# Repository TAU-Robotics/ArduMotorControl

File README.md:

# Discrete Control Lab
Discrete control experiment developed for the control lab at Tel Aviv University
The setup uses an Arduino Uno micro controller, micro dc gear motor with magnetic encoder and SparkFun Ardumoto shield.

The experiment has two parts, Simulation in simulink matlab and a hardware setup with arduino.

Simulation response:

Arduino response:

# HomeKit Motor Control

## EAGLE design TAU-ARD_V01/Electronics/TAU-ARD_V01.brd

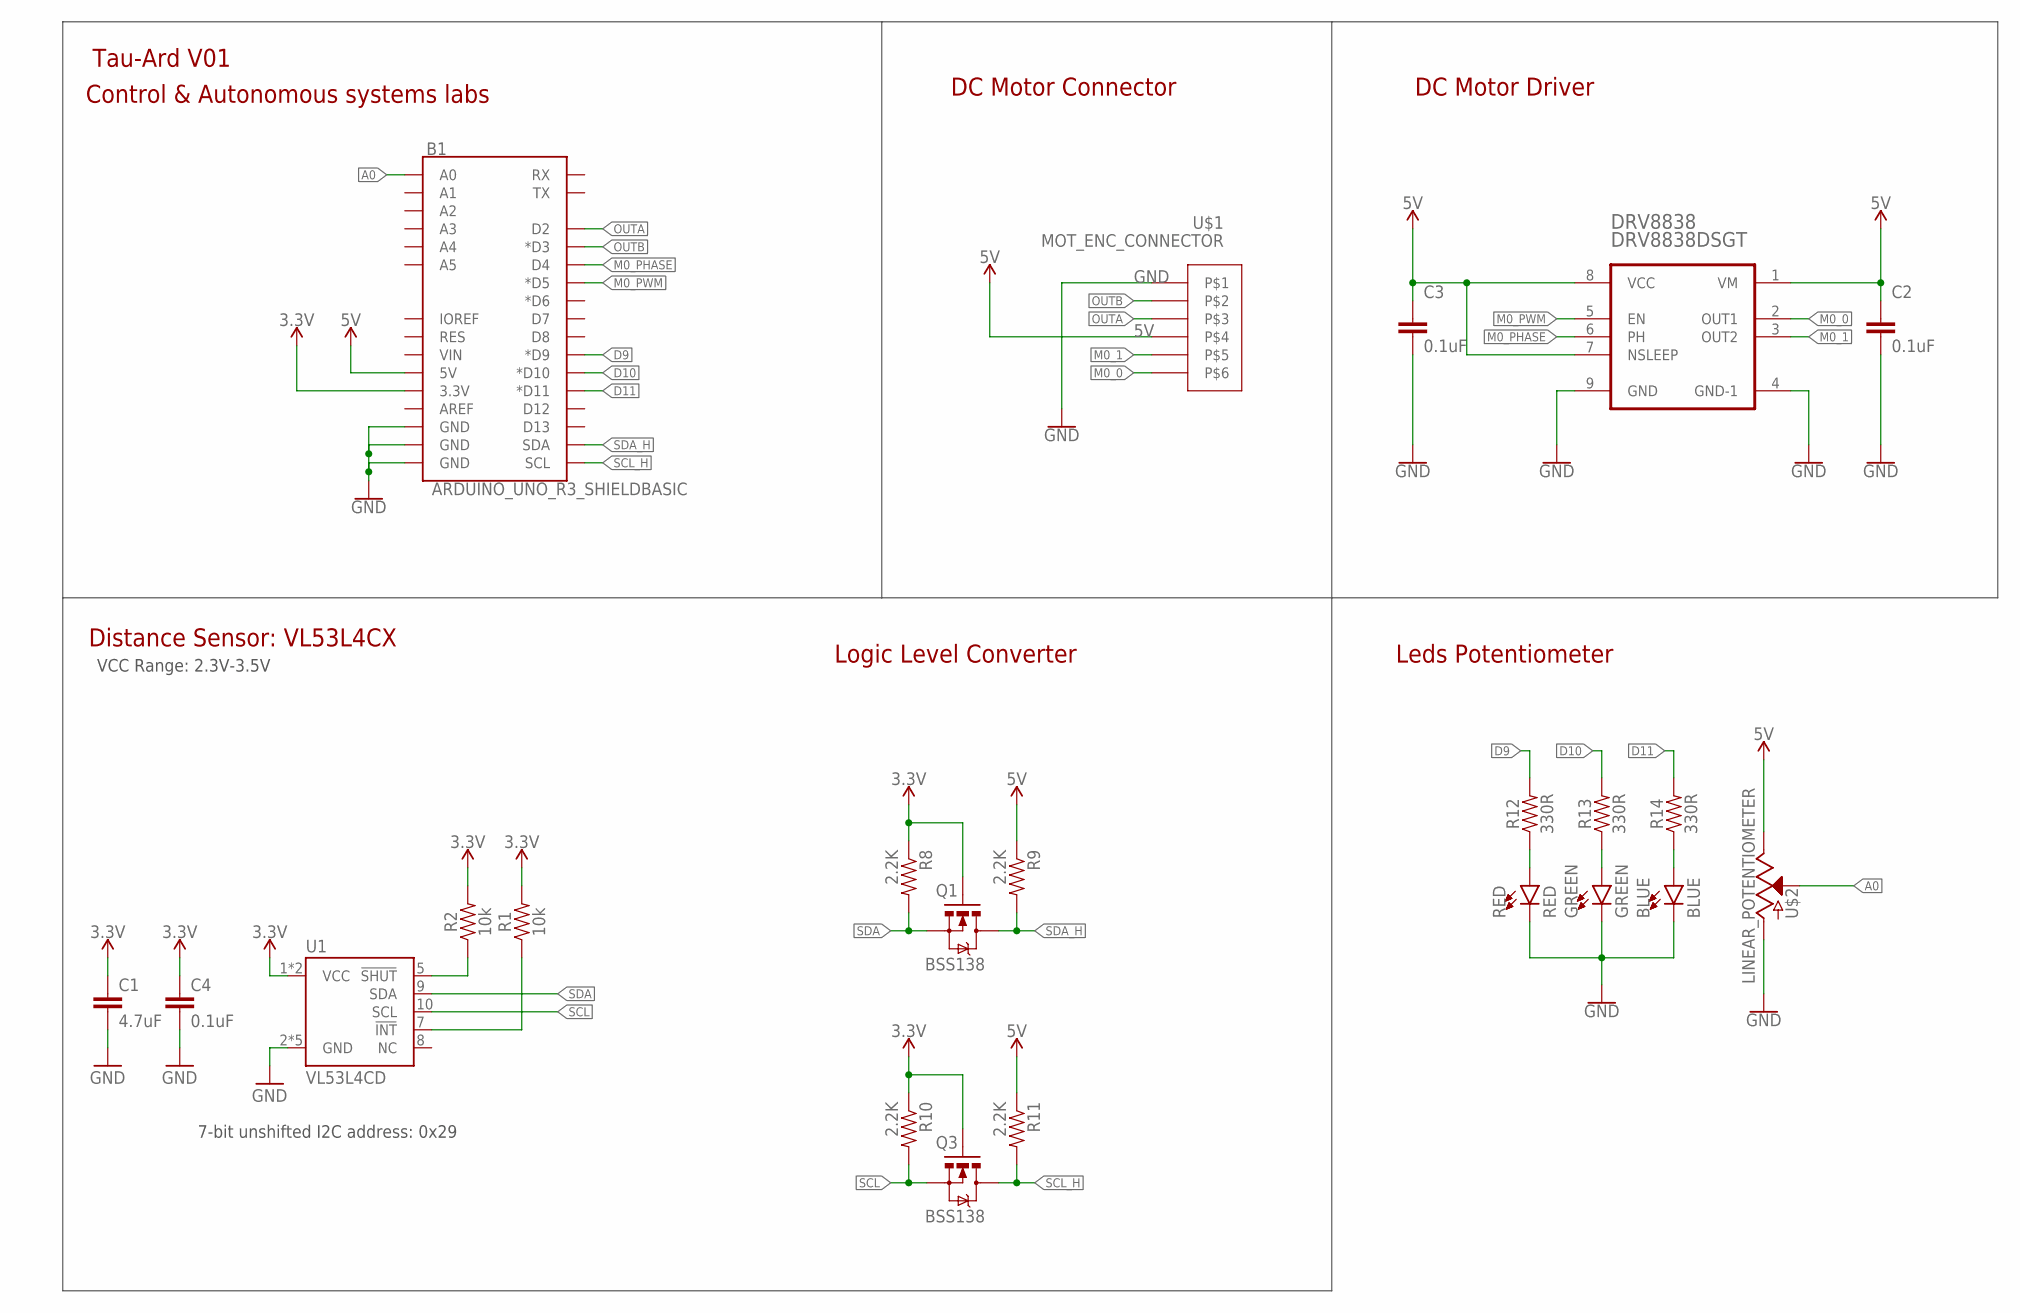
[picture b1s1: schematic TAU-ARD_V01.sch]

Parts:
B1: ARDUINO_UNO_R3_SHIELDBASIC; UNO_R3_SHIELD
BLUE: BLUE; LED-1206
C1: 4.7uF; 0603
C2, C3, C4: 0.1uF; 0603
DRV8838: DRV8838DSGT; SON50P200X200X80-9N
GREEN: GREEN; LED-1206
Q1, Q3: BSS138; SOT23-3
R1, R2: 10k; 0603
R8, R9, R10, R11: 2.2K; 0603-RES
R12, R13, R14: 330R; 0805
RED: RED; LED-1206
U1: VL53L4CD
U$1: MOT_ENC_CONNECTOR; 6X1_CONNECTOR_2MM_SMD
U$2: LINEAR_POTENTIOMETER; PTA2043

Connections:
3.3V: B1.3.3V, C1.1, C4.1, Q1.1 (G), Q3.1 (G), R1.2, R2.2, R8.1, R10.1, U1.1 (VCC), U1.11 (VCC)
5V: B1.5V, C2.1, C3.1, DRV8838.1 (VM), DRV8838.7 (NSLEEP), DRV8838.8 (VCC), R9.1, R11.1, U$1.P$4, U$2.TOP (VCC)
!INT: R1.1, U1.7 (!INT)
!SHUT: R2.1, U1.5 (!SHUT)
A0: B1.A0, U$2.WIPER (SIG)
D9: B1.D9 (*D9), R12.2
D10: B1.D10 (*D10), R13.2
D11: B1.D11 (*D11), R14.2
GND: B1.GND@0 (GND), B1.GND@1 (GND), B1.GND@2 (GND), BLUE.C, C1.2, C2.2, C3.2, C4.2, DRV8838.4 (GND-1), DRV8838.9 (GND), GREEN.C, RED.C, U1.2 (GND), U1.3 (GND), U1.4 (GND), U1.6 (GND), U1.12 (GND), U$1.P$1, U$2.BOTTOM (GND)
M0_0: DRV8838.2 (OUT1), U$1.P$6
M0_1: DRV8838.3 (OUT2), U$1.P$5
M0_PHASE: B1.D4, DRV8838.6 (PH)
M0_PWM: B1.D5 (*D5), DRV8838.5 (EN)
unnamed: R12.1, RED.A
unnamed: GREEN.A, R13.1
unnamed: BLUE.A, R14.1
OUTA: B1.D2, U$1.P$3
OUTB: B1.D3 (*D3), U$1.P$2
SCL: Q3.2 (S), R10.2, U1.10 (SCL)
SCL_H: B1.SCL, Q3.3 (D), R11.2
SDA: Q1.2 (S), R8.2, U1.9 (SDA)
SDA_H: B1.SDA, Q1.3 (D), R9.2

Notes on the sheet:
DC Motor Driver
Logic Level Converter
Tau-Ard V01
DC Motor Connector
Leds Potentiometer
Control & Autonomous systems labs
7-bit unshifted I2C address: 0x29
Distance Sensor: VL53L4CX
VCC Range: 2.3V-3.5V

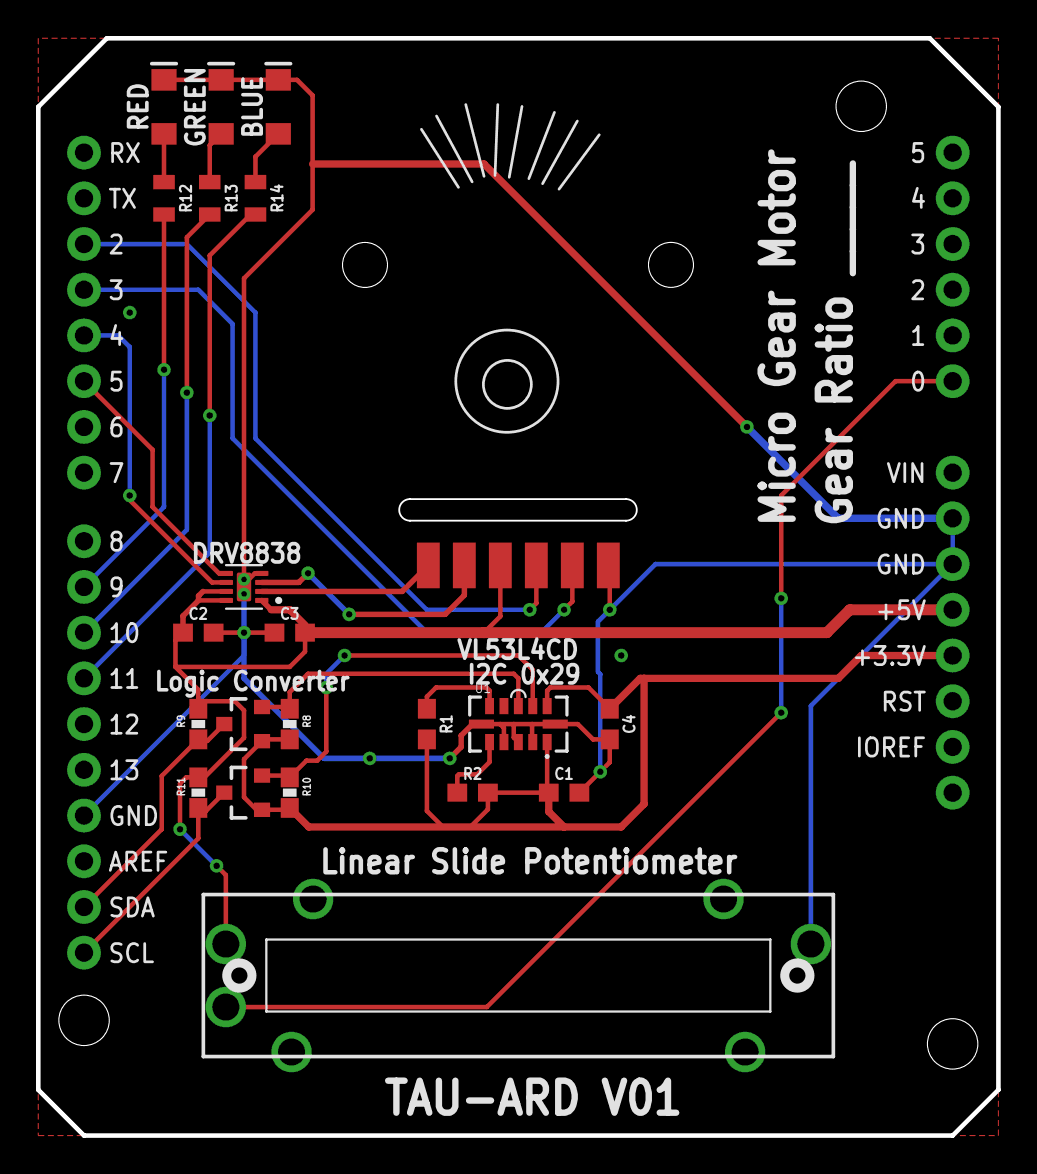
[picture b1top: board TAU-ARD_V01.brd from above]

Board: 2 copper layers, 53.3 x 61.0 mm, 23 parts (0 on the bottom side), 22 nets.

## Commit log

2020-12-10 added photos
2020-12-29 Documentation update, Maria Inputs
2021-02-14 missing files
2021-02-22 discrete control V02
    V02 - Moved gear ratio to main code, updated conversion constants accordingly, Added timeout variable
2021-04-18 gitignore
2021-06-20 V02 Updates
2021-06-24 DiscreteControl v02
2021-06-28 fix library
    fix to correct initialize of encoder reading values.
2021-06-28 fixes
2021-06-28 model update
2021-07-26 coil response
2022-05-10 TAU-ARD
2022-06-20 bug fixes
2022-08-14 images

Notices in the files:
parts and their libraries:
SparkFun-Boards: Licensing: Creative Commons ShareAlike 4.0 International - https://creativecommons.org/licenses/by-sa/4.0
